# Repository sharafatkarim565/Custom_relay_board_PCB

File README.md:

# Custom_relay_board_PCB
Custom relay board design using different  MCU 

#1-Channel relay using Nano

#2-Channel relay using Nano

#4-Channel relay using Mega

#8-Channel relay using Mega

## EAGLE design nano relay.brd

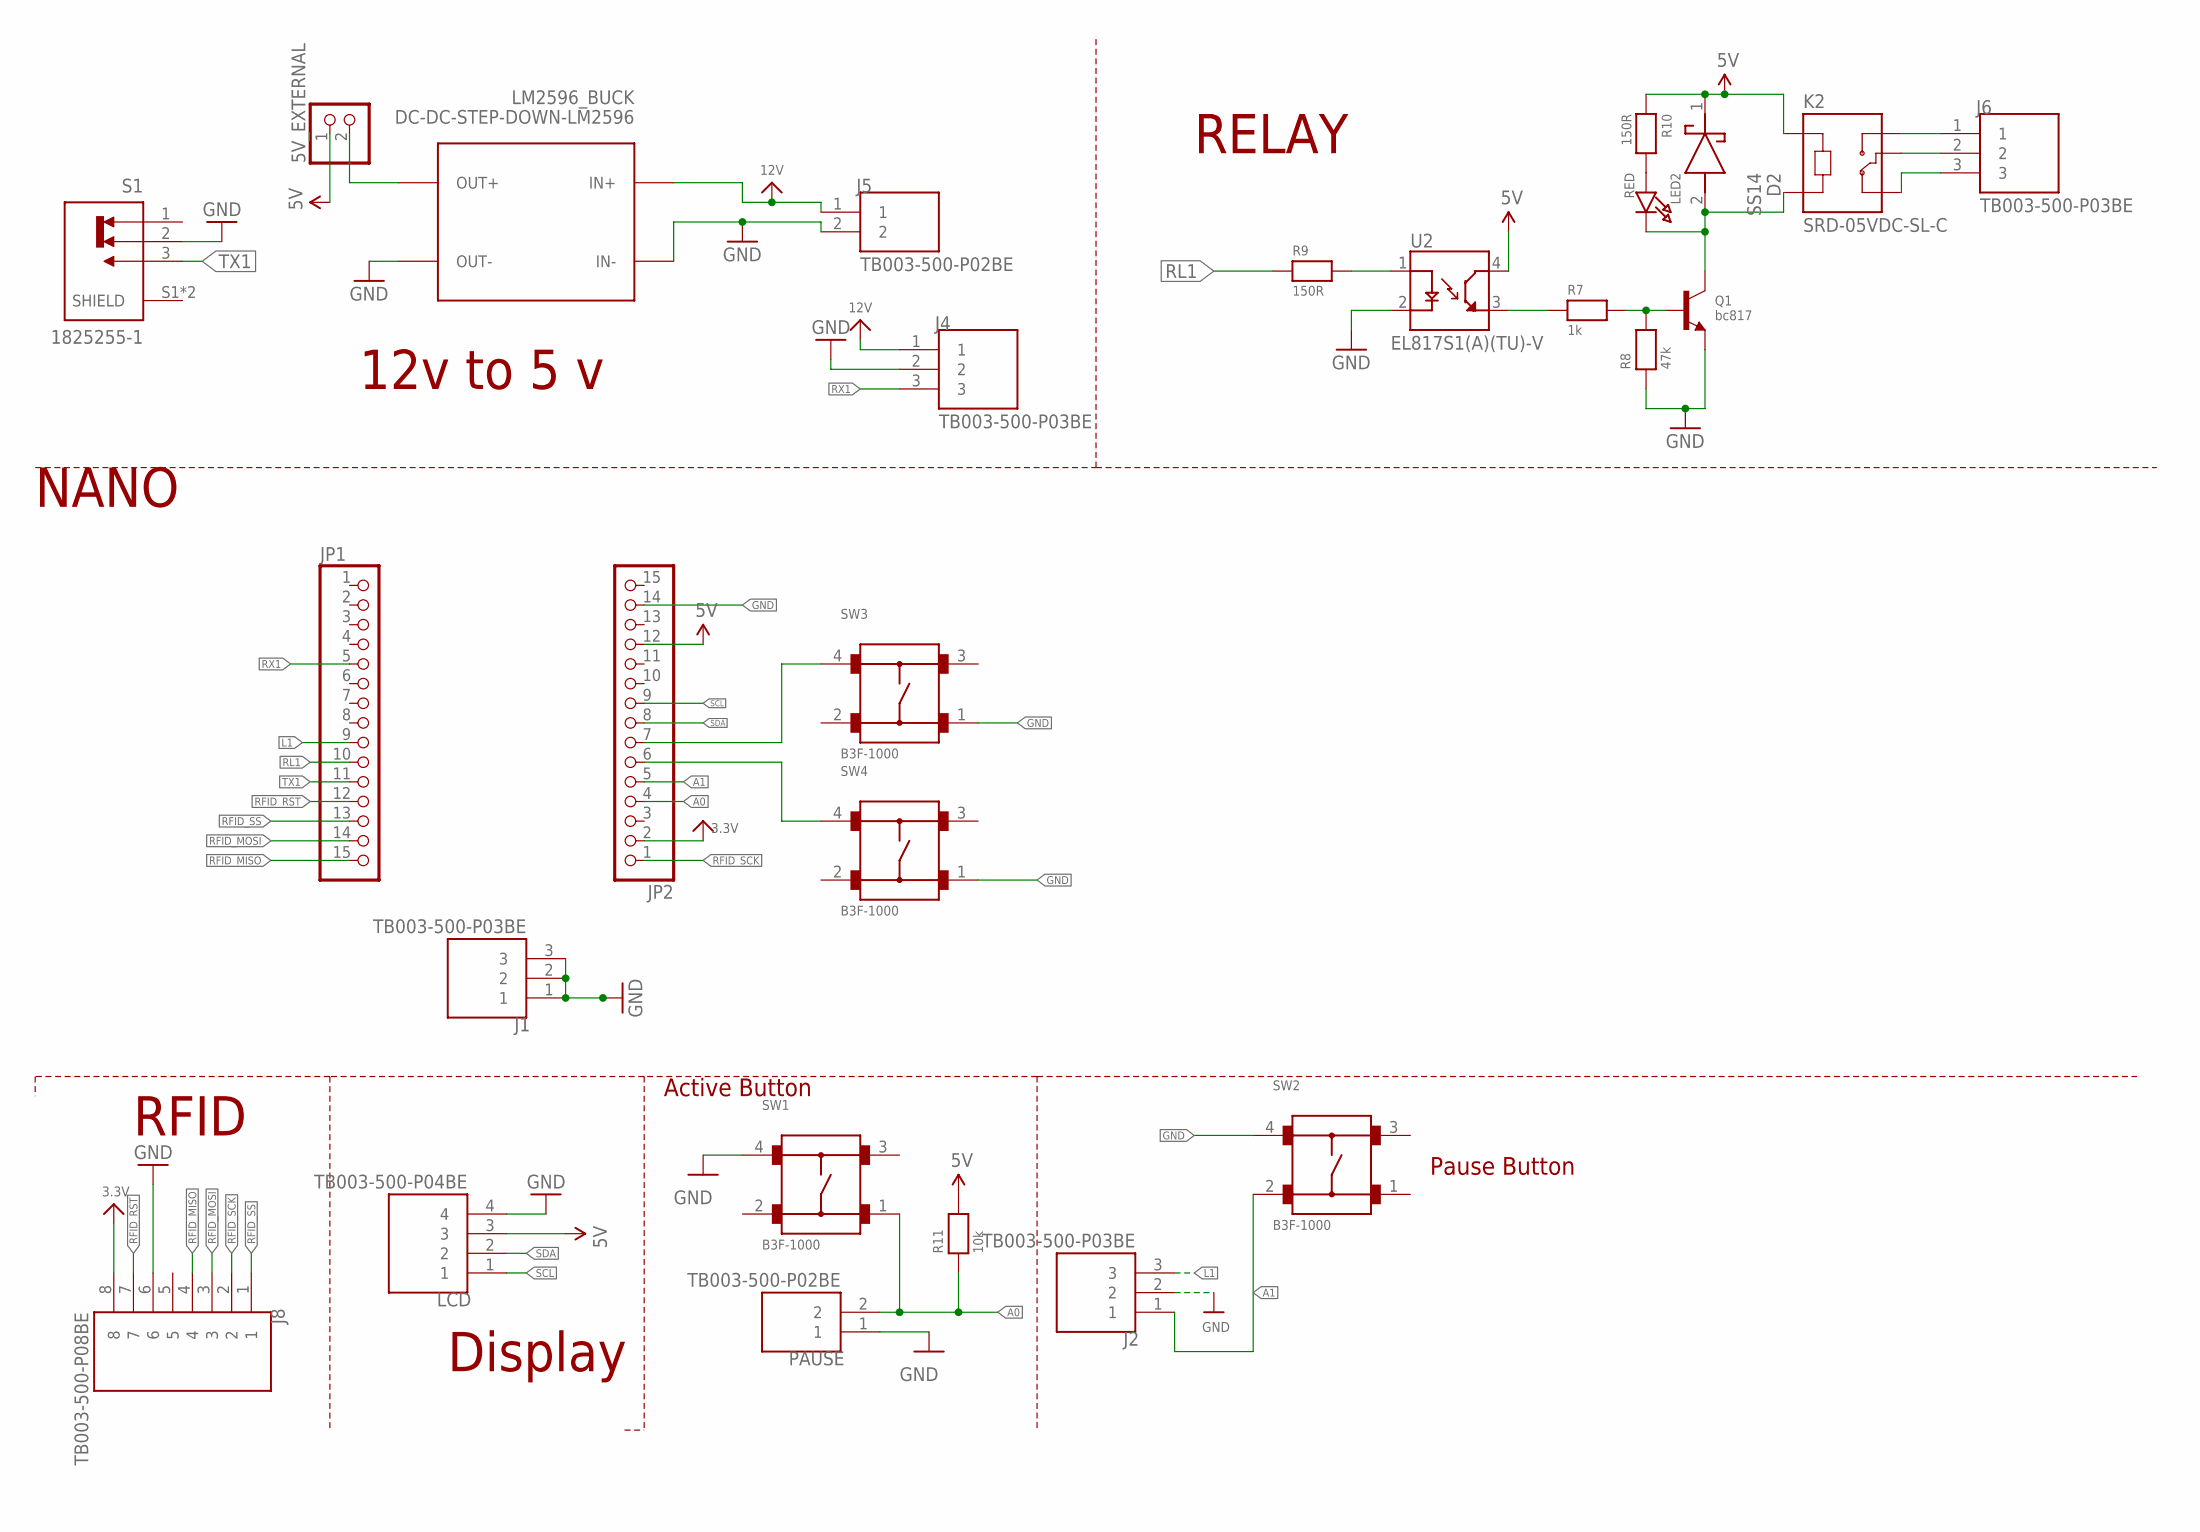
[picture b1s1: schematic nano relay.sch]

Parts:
5V_EXTERNAL: HEADER-1X2ROUND; 1X02_ROUND
D2: SS14; DIOM5227X270N
J1, J2, J4, J6: TB003-500-P03BE; CUI_TB003-500-P03BE
J5: TB003-500-P02BE; CUI_TB003-500-P02BE
J8: TB003-500-P08BE; CUI_TB003-500-P08BE
JP1, JP2: HEADER-1X15; 1X15_ROUND_70
K2: SRD-05VDC-SL-C; RELAY_SRD-05VDC-SL-C
LCD: TB003-500-P04BE; CUI_TB003-500-P04BE
LED2: RED; CHIPLED_0603
LM2596_BUCK: DC-DC-STEP-DOWN-LM2596
PAUSE: TB003-500-P02BE; CUI_TB003-500-P02BE
Q1: bc817; SOT23-R
R7: 1k; 0603
R8: 47k; 0603
R9: 150R; 0603
R10: 150R; 0402
R11: 10k; 0603
S1: 1825255-1; SW_1825255-1
SW1, SW2, SW3, SW4: B3F-1000
U2: EL817S1(A)(TU)-V; SOIC254P1030X390-4N_EL817S1(A)(TU)-V

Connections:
3.3V: J8.8, JP2.2
5V: 5V_EXTERNAL.1, D2.1 (K), JP2.12, K2.A1, LCD.3, R10.1, R11.2, U2.4 (CT)
12V: J4.1, J5.1, LM2596_BUCK.IN+
A0: JP2.4, PAUSE.2, R11.1, SW1.1
A1: J2.1, JP2.5, SW2.2
GND: J1.1, J1.2, J1.3, J2.2, J4.2, J5.2, J8.6, JP2.14, LCD.4, LM2596_BUCK.IN-, LM2596_BUCK.OUT-, PAUSE.1, Q1.2 (E), R8.1, S1.2, SW1.4, SW2.4, SW3.1, SW4.1, U2.2 (C)
L1: J2.3, JP1.9
unnamed: JP2.7, SW3.4
unnamed: J6.1, K2.NO
unnamed: LED2.A, R10.2
unnamed: JP2.6, SW4.4
unnamed: J6.2, K2.COM
unnamed: D2.2 (A), K2.A2, LED2.C, Q1.3 (C)
unnamed: Q1.1 (B), R7.2, R8.2
unnamed: J6.3, K2.NC
unnamed: R7.1, U2.3 (ET)
unnamed: 5V_EXTERNAL.2, LM2596_BUCK.OUT+
unnamed: R9.2, U2.1 (A)
RFID_MISO: J8.4, JP1.15
RFID_MOSI: J8.3, JP1.14
RFID_RST: J8.7, JP1.12
RFID_SCK: J8.2, JP2.1
RFID_SS: J8.1, JP1.13
RL1: JP1.10, R9.1
RX1: J4.3, JP1.5
SCL: JP2.9, LCD.1
SDA: JP2.8, LCD.2
TX1: JP1.11, S1.3

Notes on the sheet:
12v to 5 v
Display
RFID
RELAY
NANO
Active Button
Pause Button

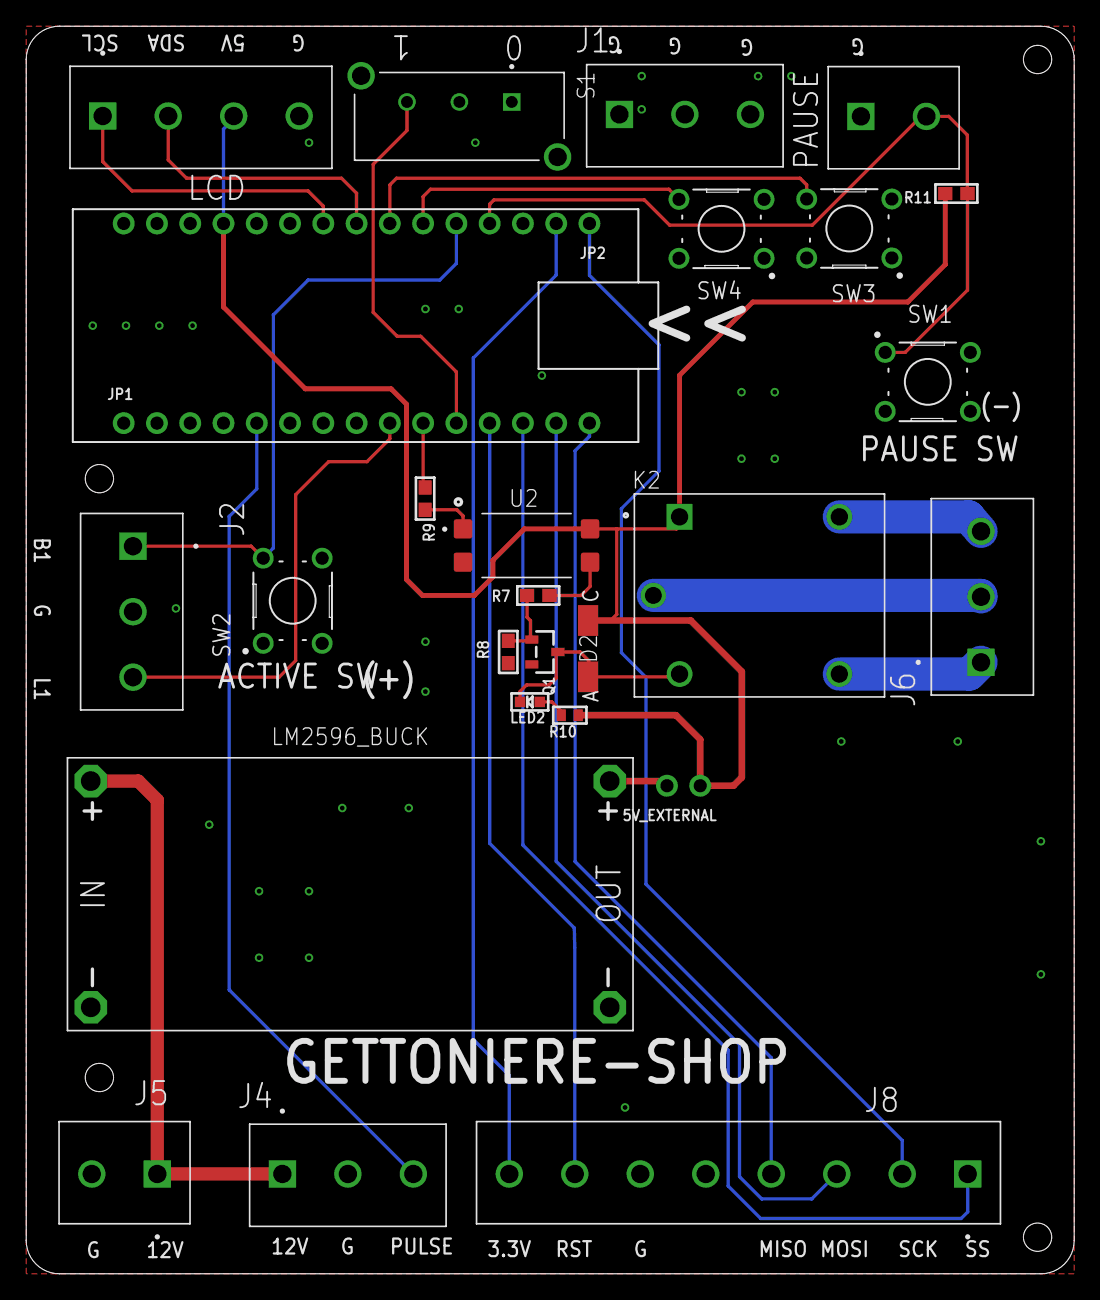
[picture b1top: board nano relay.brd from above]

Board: 2 copper layers, 80.0 x 95.2 mm, 27 parts (0 on the bottom side), 28 nets.

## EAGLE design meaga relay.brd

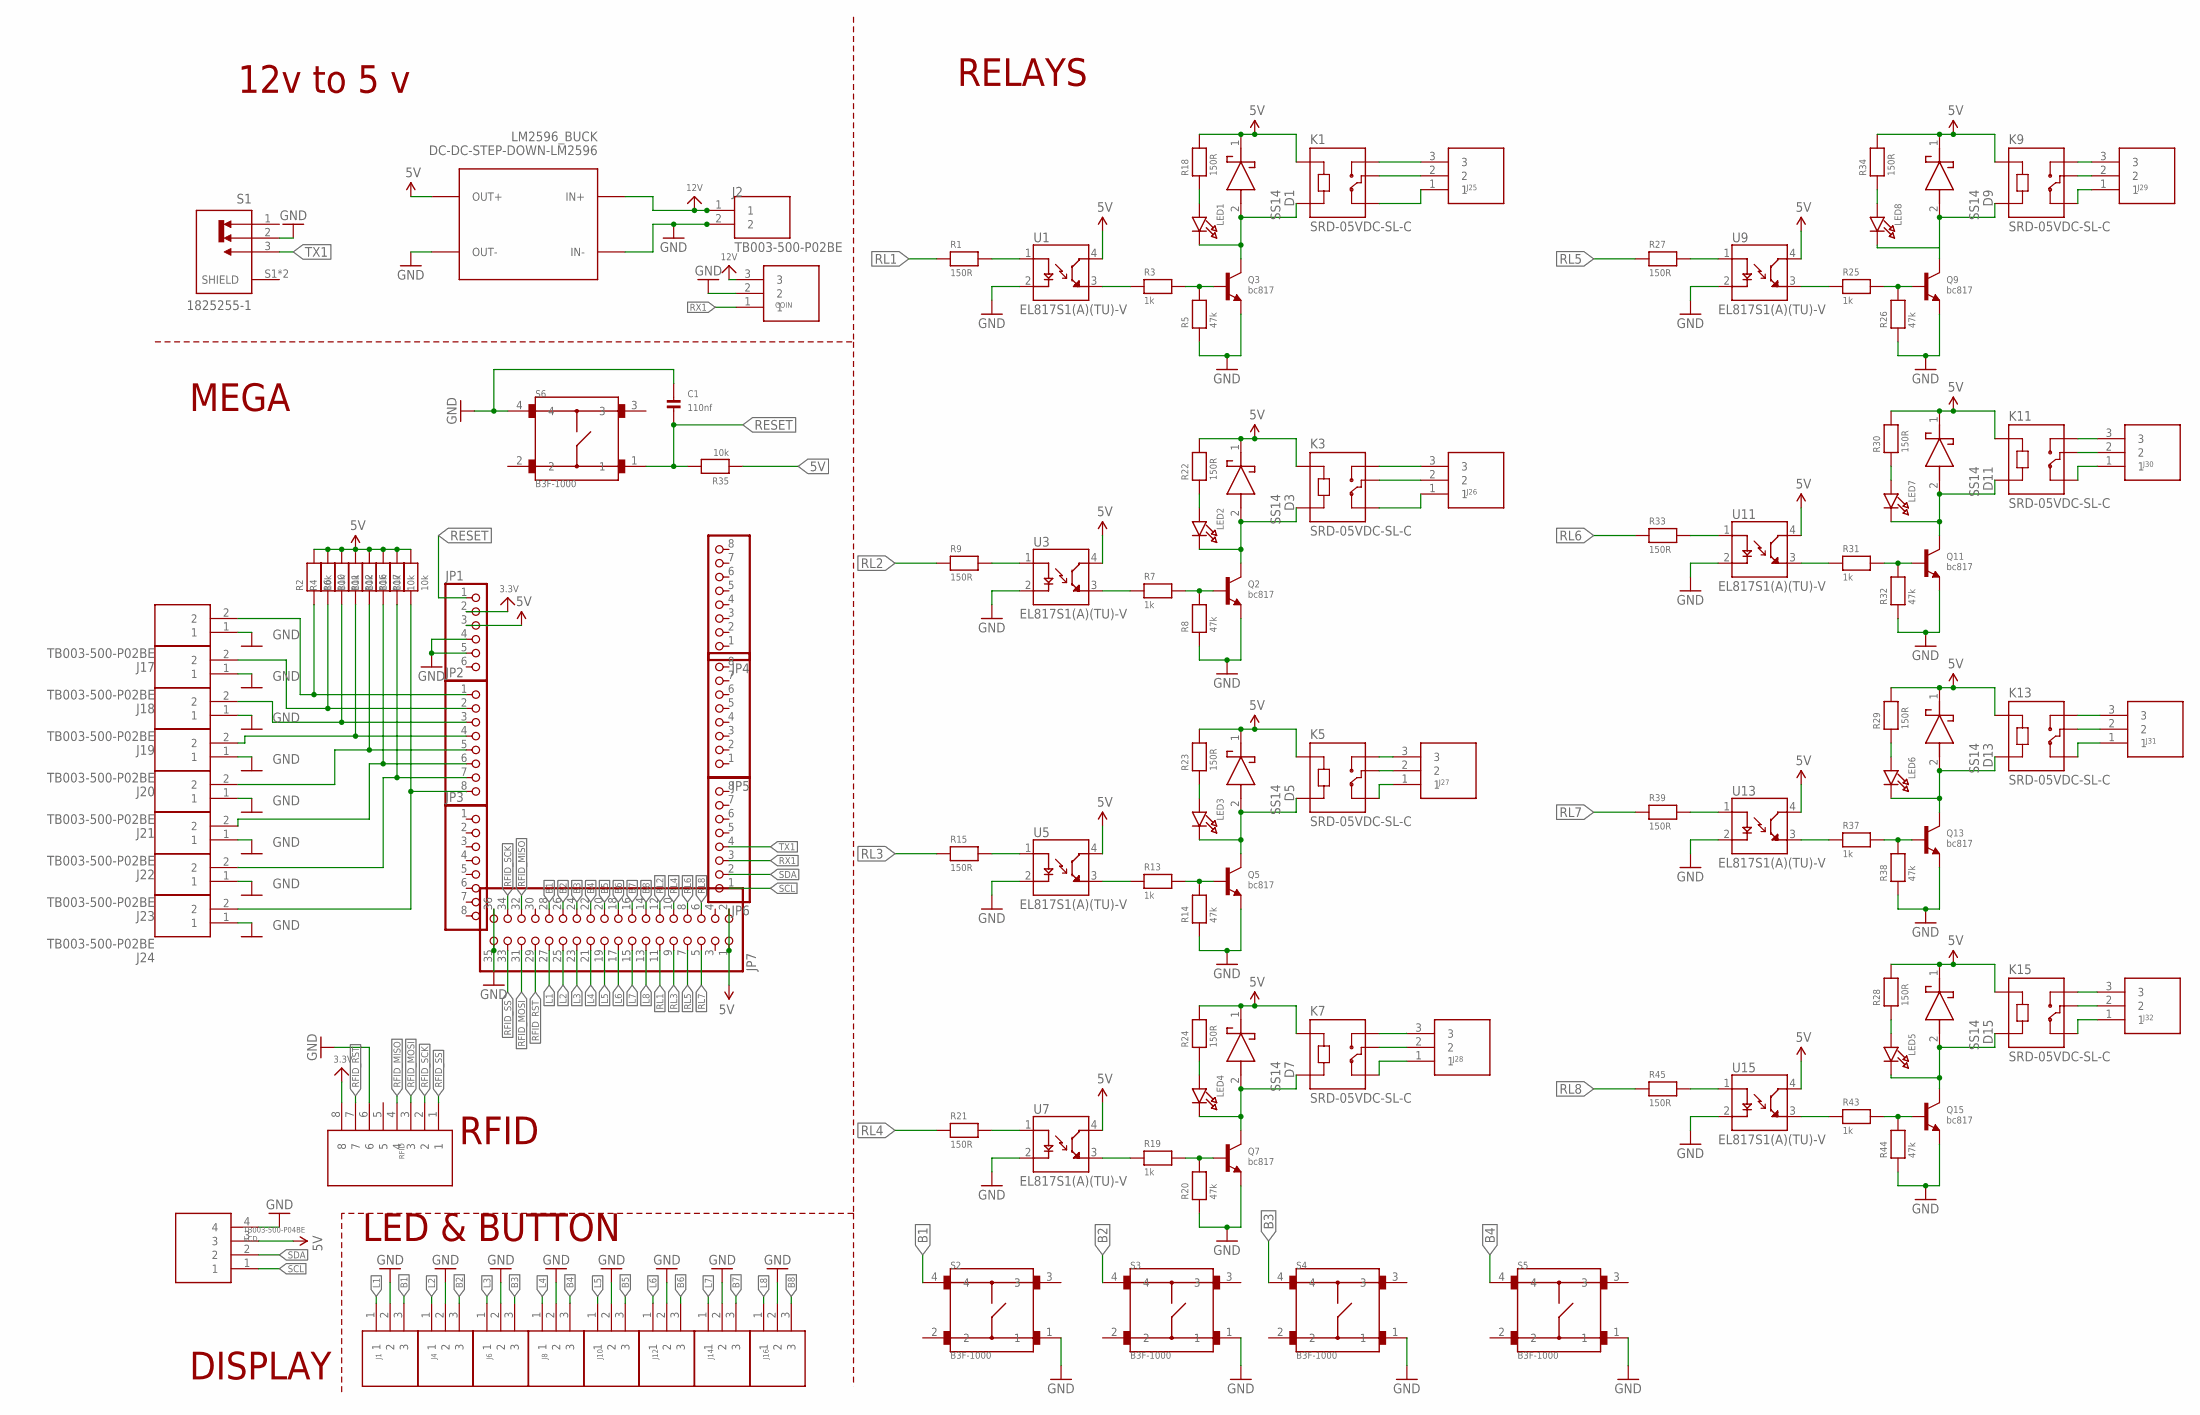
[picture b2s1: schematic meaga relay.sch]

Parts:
C1: 110nf; 0603
COIN: TB003-500-P03BE; CUI_TB003-500-P03BE
D1, D3, D5, D7, D9, D11, D13, D15: SS14; DIOM5227X270N
J1, J4, J6, J8, J10, J12, J14, J16, J25, J26, J27, J28, J29, J30, J31, J32: TB003-500-P03BE; CUI_TB003-500-P03BE
J2, J17, J18, J19, J20, J21, J22, J23, J24: TB003-500-P02BE; CUI_TB003-500-P02BE
JP1: PINHD-1X6; 1X06
JP2, JP3, JP4, JP5, JP6: PINHD-1X8; 1X08
JP7: PINHD-2X18; 2X18
K1, K3, K5, K7, K9, K11, K13, K15: SRD-05VDC-SL-C; RELAY_SRD-05VDC-SL-C
LCD: TB003-500-P04BE; CUI_TB003-500-P04BE
LED1, LED2, LED3, LED4, LED5, LED6, LED7, LED8: LED0603; CHIPLED_0603
LM2596_BUCK: DC-DC-STEP-DOWN-LM2596
Q2, Q3, Q5, Q7, Q9, Q11, Q13, Q15: bc817; SOT23-R
R1, R9, R15, R21, R27, R33, R39, R45: 150R; 0603
R2, R4, R6, R10, R11, R12, R16, R17: 10k; 0603
R3, R7, R13, R19, R25, R31, R37, R43: 1k; 0603
R5, R8, R14, R20, R26, R32, R38, R44: 47k; 0603
R18, R22, R23, R24, R28, R29, R30, R34: 150R; 0402
R35: 10k; 0402
RFID: TB003-500-P08BE; CUI_TB003-500-P08BE
S1: 1825255-1; SW_1825255-1
S2, S3, S4, S5, S6: B3F-1000; SW_B3F-1000
U1, U3, U5, U7, U9, U11, U13, U15: EL817S1(A)(TU)-V; SOIC254P1030X390-4N_EL817S1(A)(TU)-V

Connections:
3.3V: JP1.2, RFID.8
5V: D1.1 (K), D3.1 (K), D5.1 (K), D7.1 (K), D9.1 (K), D11.1 (K), D13.1 (K), D15.1 (K), JP1.3, JP7.1, JP7.2, K1.A1, K3.A1, K5.A1, K7.A1, K9.A1, K11.A1, K13.A1, K15.A1, LCD.3, LM2596_BUCK.OUT+, R2.2, R4.2, R6.2, R10.2, R11.2, R12.2, R16.2, R17.2, R18.2, R22.2, R23.2, R24.2, R28.2, R29.2, R30.2, R34.2, R35.1, U1.4 (CT), U3.4 (CT), U5.4 (CT), U7.4 (CT), U9.4 (CT), U11.4 (CT), U13.4 (CT), U15.4 (CT)
12V: COIN.3, J2.1, LM2596_BUCK.IN+
B1: J1.3, JP7.28, S2.4
B2: J4.3, JP7.26, S3.4
B3: J6.3, JP7.24, S4.4
B4: J8.3, JP7.22, S5.4
B5: J10.3, JP7.20
B6: J12.3, JP7.18
B7: J14.3, JP7.16
B8: J16.3, JP7.14
GND: C1.1, COIN.2, J1.2, J2.2, J4.2, J6.2, J8.2, J10.2, J12.2, J14.2, J16.2, J17.1, J18.1, J19.1, J20.1, J21.1, J22.1, J23.1, J24.1, JP1.4, JP1.5, JP7.35, JP7.36, LCD.4, LM2596_BUCK.IN-, LM2596_BUCK.OUT-, Q2.2 (E), Q3.2 (E), Q5.2 (E), Q7.2 (E), Q9.2 (E), Q11.2 (E), Q13.2 (E), Q15.2 (E), R5.1, R8.1, R14.1, R20.1, R26.1, R32.1, R38.1, R44.1, RFID.6, S1.2, S2.1, S3.1, S4.1, S5.1, S6.4, U1.2 (C), U3.2 (C), U5.2 (C), U7.2 (C), U9.2 (C), U11.2 (C), U13.2 (C), U15.2 (C)
L1: J1.1, JP7.27
L2: J4.1, JP7.25
L3: J6.1, JP7.23
L4: J8.1, JP7.21
L5: J10.1, JP7.19
L6: J12.1, JP7.17
L7: J14.1, JP7.15
L8: J16.1, JP7.13
unnamed: R3.1, U1.3 (ET)
unnamed: R1.2, U1.1 (A)
unnamed: J25.1, K1.NC
unnamed: J17.2, JP2.1, R2.1
unnamed: J18.2, JP2.2, R4.1
unnamed: J19.2, JP2.3, R6.1
unnamed: J20.2, JP2.4, R10.1
unnamed: J21.2, JP2.5, R11.1
unnamed: D1.2 (A), K1.A2, LED1.C, Q3.3 (C)
unnamed: J22.2, JP2.6, R12.1
unnamed: D3.2 (A), K3.A2, LED2.C, Q2.3 (C)
unnamed: Q2.1 (B), R7.2, R8.2
unnamed: J26.3, K3.NO
unnamed: R7.1, U3.3 (ET)
unnamed: Q3.1 (B), R3.2, R5.2
unnamed: R9.2, U3.1 (A)
unnamed: J26.1, K3.NC
unnamed: J25.3, K1.NO
unnamed: J23.2, JP2.7, R16.1
unnamed: J24.2, JP2.8, R17.1
unnamed: J27.1, K5.NC
unnamed: J28.1, K7.NC
unnamed: J25.2, K1.COM
unnamed: J26.2, K3.COM
unnamed: D5.2 (A), K5.A2, LED3.C, Q5.3 (C)
unnamed: Q5.1 (B), R13.2, R14.2
unnamed: J27.3, K5.NO
unnamed: R13.1, U5.3 (ET)
unnamed: R15.2, U5.1 (A)
unnamed: J32.1, K15.NC
unnamed: J29.2, K9.COM
unnamed: J30.2, K11.COM
unnamed: J32.2, K15.COM
unnamed: J31.2, K13.COM
unnamed: J28.2, K7.COM
unnamed: J27.2, K5.COM
unnamed: D7.2 (A), K7.A2, LED4.C, Q7.3 (C)
unnamed: Q7.1 (B), R19.2, R20.2
unnamed: J28.3, K7.NO
unnamed: R19.1, U7.3 (ET)
unnamed: R21.2, U7.1 (A)
unnamed: J31.1, K13.NC
unnamed: J30.1, K11.NC
unnamed: J29.1, K9.NC
unnamed: LED2.A, R22.1
unnamed: LED3.A, R23.1
unnamed: LED4.A, R24.1
unnamed: LED5.A, R28.1
unnamed: D9.2 (A), K9.A2, LED8.C, Q9.3 (C)
unnamed: Q9.1 (B), R25.2, R26.2
unnamed: J29.3, K9.NO
unnamed: R25.1, U9.3 (ET)
unnamed: R27.2, U9.1 (A)
unnamed: LED6.A, R29.1
unnamed: LED7.A, R30.1
unnamed: LED8.A, R34.1
unnamed: LED1.A, R18.1
unnamed: D11.2 (A), K11.A2, LED7.C, Q11.3 (C)
unnamed: Q11.1 (B), R31.2, R32.2
unnamed: J30.3, K11.NO
unnamed: R31.1, U11.3 (ET)
unnamed: R33.2, U11.1 (A)
unnamed: D13.2 (A), K13.A2, LED6.C, Q13.3 (C)
unnamed: Q13.1 (B), R37.2, R38.2
unnamed: J31.3, K13.NO
unnamed: R37.1, U13.3 (ET)
unnamed: R39.2, U13.1 (A)
unnamed: D15.2 (A), K15.A2, LED5.C, Q15.3 (C)
unnamed: Q15.1 (B), R43.2, R44.2
unnamed: J32.3, K15.NO
unnamed: R43.1, U15.3 (ET)
unnamed: R45.2, U15.1 (A)
RESET: C1.2, JP1.1, R35.2, S6.1
RFID_MISO: JP7.32, RFID.4
RFID_MOSI: JP7.31, RFID.3
RFID_RST: JP7.29, RFID.7
RFID_SCK: JP7.34, RFID.2
RFID_SS: JP7.33, RFID.1
RL1: JP7.11, R1.1
RL2: JP7.12, R9.1
RL3: JP7.9, R15.1
RL4: JP7.10, R21.1
RL5: JP7.7, R27.1
RL6: JP7.8, R33.1
RL7: JP7.5, R39.1
RL8: JP7.6, R45.1
RX1: COIN.1, JP6.3
SCL: JP6.1, LCD.1
SDA: JP6.2, LCD.2
TX1: JP6.4, S1.3

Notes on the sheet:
RELAYS
12v to 5 v
MEGA
LED & BUTTON
DISPLAY
RFID

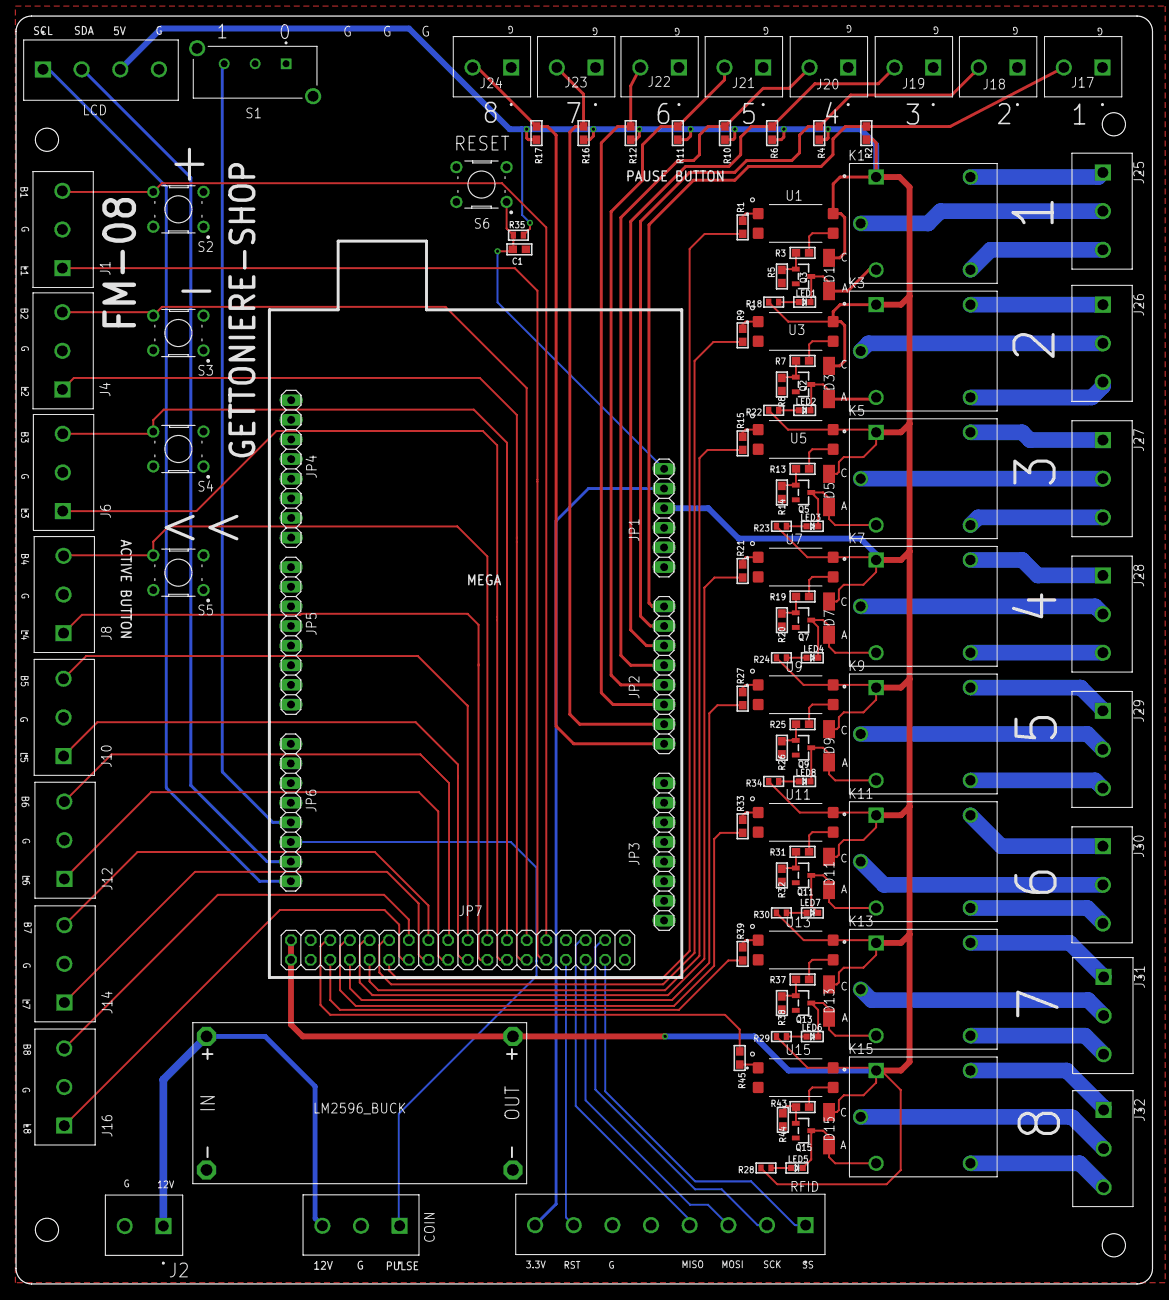
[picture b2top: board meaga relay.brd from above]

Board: 2 copper layers, 147.0 x 164.0 mm, 124 parts (0 on the bottom side), 110 nets.

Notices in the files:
parts and their libraries:
microbuilder: This work is placed in the public domain, and may be freely used for commercial and non-commercial work with the following conditions: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
diy-modules: Released under the Creative Commons Attribution 4.0 International License: http://creativecommons.org/licenses/by/4.0
